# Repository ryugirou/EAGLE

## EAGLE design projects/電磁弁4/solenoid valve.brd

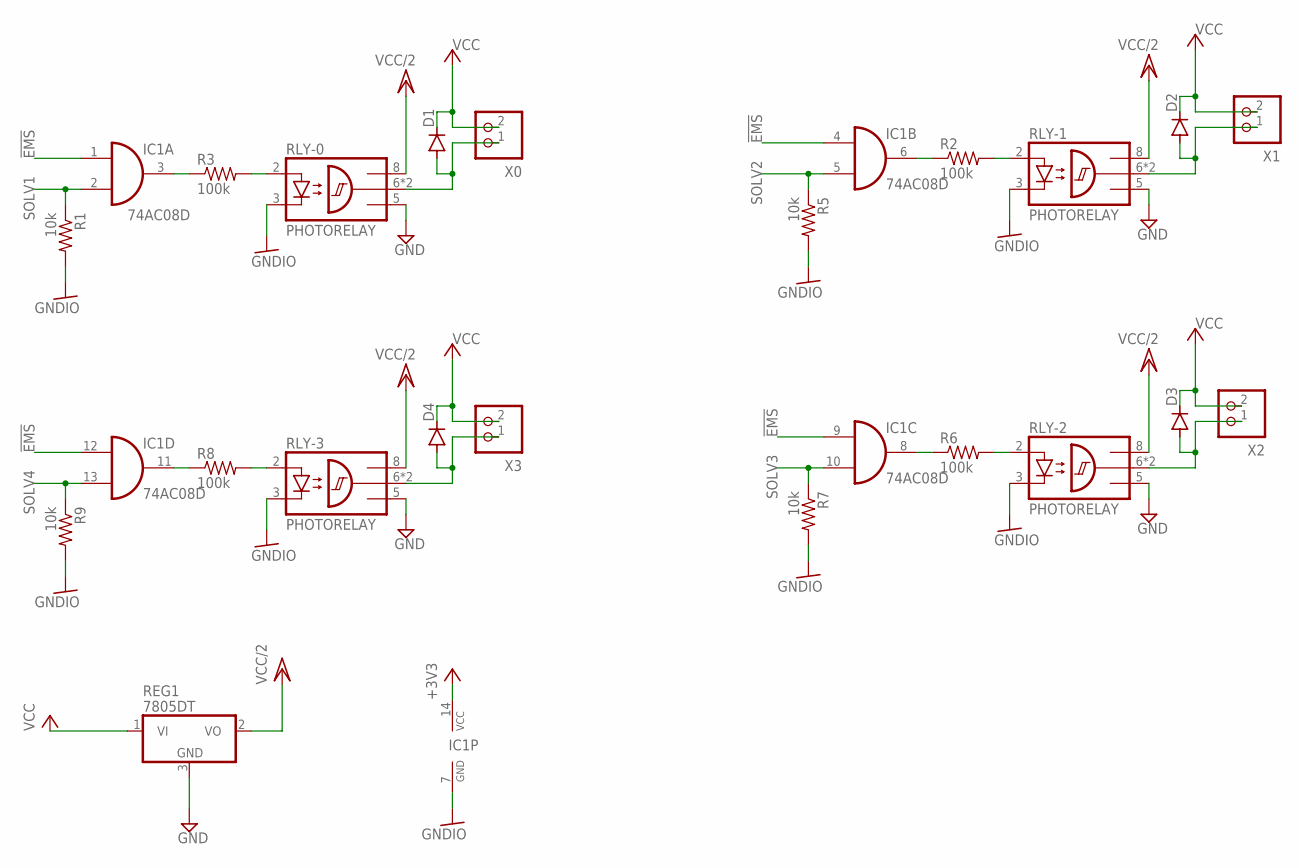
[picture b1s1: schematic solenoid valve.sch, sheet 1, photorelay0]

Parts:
D1, D2, D3, D4: DIODE-SOD123; SOD123
IC1: 74AC08D; SO14
R1, R5, R7, R9: 10k; R0603
R2, R3, R6, R8: 100k; R0603
REG1: 7805DT; TO252
RLY-0, RLY-1, RLY-2, RLY-3: PHOTORELAY; SOP254P1016X385-8
X0, X1, X2, X3: S2B-XH-A

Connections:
!EMS: IC1.1 (I0), IC1.4 (I0), IC1.9 (I0), IC1.12 (I0); also elsewhere on the board
+3V3: IC1.14 (VCC); also elsewhere on the board
GND: REG1.3 (GND), RLY-0.5 (GND), RLY-1.5 (GND), RLY-2.5 (GND), RLY-3.5 (GND); also elsewhere on the board
GNDIO: IC1.7 (GND), R1.2, R5.2, R7.2, R9.2, RLY-0.3 (C), RLY-1.3 (C), RLY-2.3 (C), RLY-3.3 (C); also elsewhere on the board
unnamed: D2.A, RLY-1.6 (OUT), RLY-1.7 (OUT), X1.1
unnamed: R2.2, RLY-1.2 (A)
unnamed: D1.A, RLY-0.6 (OUT), RLY-0.7 (OUT), X0.1
unnamed: IC1.6 (O), R2.1
unnamed: D3.A, RLY-2.6 (OUT), RLY-2.7 (OUT), X2.1
unnamed: R3.2, RLY-0.2 (A)
unnamed: IC1.3 (O), R3.1
unnamed: R6.2, RLY-2.2 (A)
unnamed: IC1.8 (O), R6.1
unnamed: D4.A, RLY-3.6 (OUT), RLY-3.7 (OUT), X3.1
unnamed: R8.2, RLY-3.2 (A)
unnamed: IC1.11 (O), R8.1
SOLV1: IC1.2 (I1), R1.1; also elsewhere on the board
SOLV2: IC1.5 (I1), R5.1; also elsewhere on the board
SOLV3: IC1.10 (I1), R7.1; also elsewhere on the board
SOLV4: IC1.13 (I1), R9.1; also elsewhere on the board
VCC: D1.C, D2.C, D3.C, D4.C, REG1.1 (VI), X0.2, X1.2, X2.2, X3.2; also elsewhere on the board
VCC/2: REG1.2 (VO), RLY-0.8 (VCC), RLY-1.8 (VCC), RLY-2.8 (VCC), RLY-3.8 (VCC); also elsewhere on the board

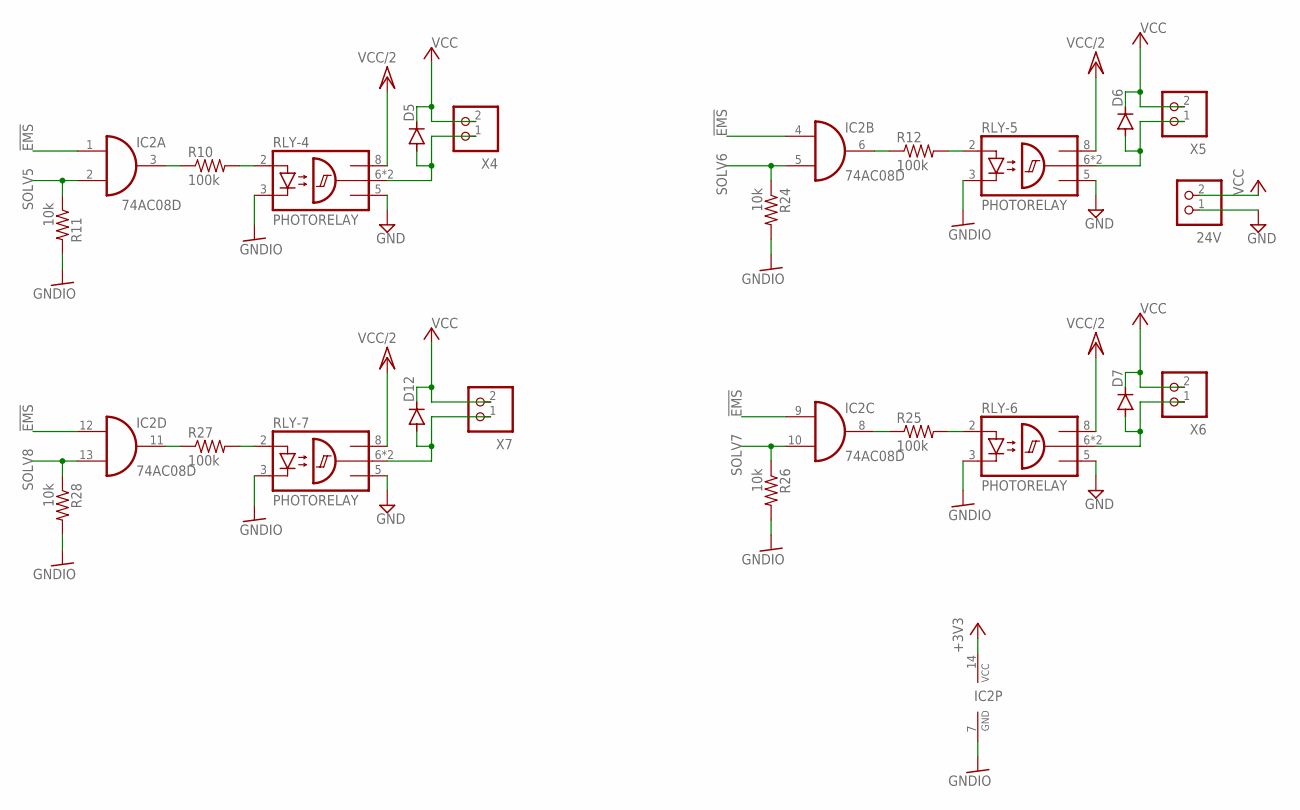
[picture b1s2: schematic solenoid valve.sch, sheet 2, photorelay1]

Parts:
24V: S2B-XH-A
D5, D6, D7, D12: DIODE-SOD123; SOD123
IC2: 74AC08D; SO14
R10, R12, R25, R27: 100k; R0603
R11, R24, R26, R28: 10k; R0603
RLY-4, RLY-5, RLY-6, RLY-7: PHOTORELAY; SOP254P1016X385-8
X4, X5, X6, X7: S2B-XH-A

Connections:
!EMS: IC2.1 (I0), IC2.4 (I0), IC2.9 (I0), IC2.12 (I0); also elsewhere on the board
+3V3: IC2.14 (VCC); also elsewhere on the board
GND: 24V.1, RLY-4.5 (GND), RLY-5.5 (GND), RLY-6.5 (GND), RLY-7.5 (GND); also elsewhere on the board
GNDIO: IC2.7 (GND), R11.2, R24.2, R26.2, R28.2, RLY-4.3 (C), RLY-5.3 (C), RLY-6.3 (C), RLY-7.3 (C); also elsewhere on the board
unnamed: D5.A, RLY-4.6 (OUT), RLY-4.7 (OUT), X4.1
unnamed: R10.2, RLY-4.2 (A)
unnamed: IC2.3 (O), R10.1
unnamed: D6.A, RLY-5.6 (OUT), RLY-5.7 (OUT), X5.1
unnamed: R12.2, RLY-5.2 (A)
unnamed: IC2.6 (O), R12.1
unnamed: D7.A, RLY-6.6 (OUT), RLY-6.7 (OUT), X6.1
unnamed: R25.2, RLY-6.2 (A)
unnamed: IC2.8 (O), R25.1
unnamed: D12.A, RLY-7.6 (OUT), RLY-7.7 (OUT), X7.1
unnamed: R27.2, RLY-7.2 (A)
unnamed: IC2.11 (O), R27.1
SOLV5: IC2.2 (I1), R11.1; also elsewhere on the board
SOLV6: IC2.5 (I1), R24.1; also elsewhere on the board
SOLV7: IC2.10 (I1), R26.1; also elsewhere on the board
SOLV8: IC2.13 (I1), R28.1; also elsewhere on the board
VCC: 24V.2, D5.C, D6.C, D7.C, D12.C, X4.2, X5.2, X6.2, X7.2; also elsewhere on the board
VCC/2: RLY-4.8 (VCC), RLY-5.8 (VCC), RLY-6.8 (VCC), RLY-7.8 (VCC); also elsewhere on the board

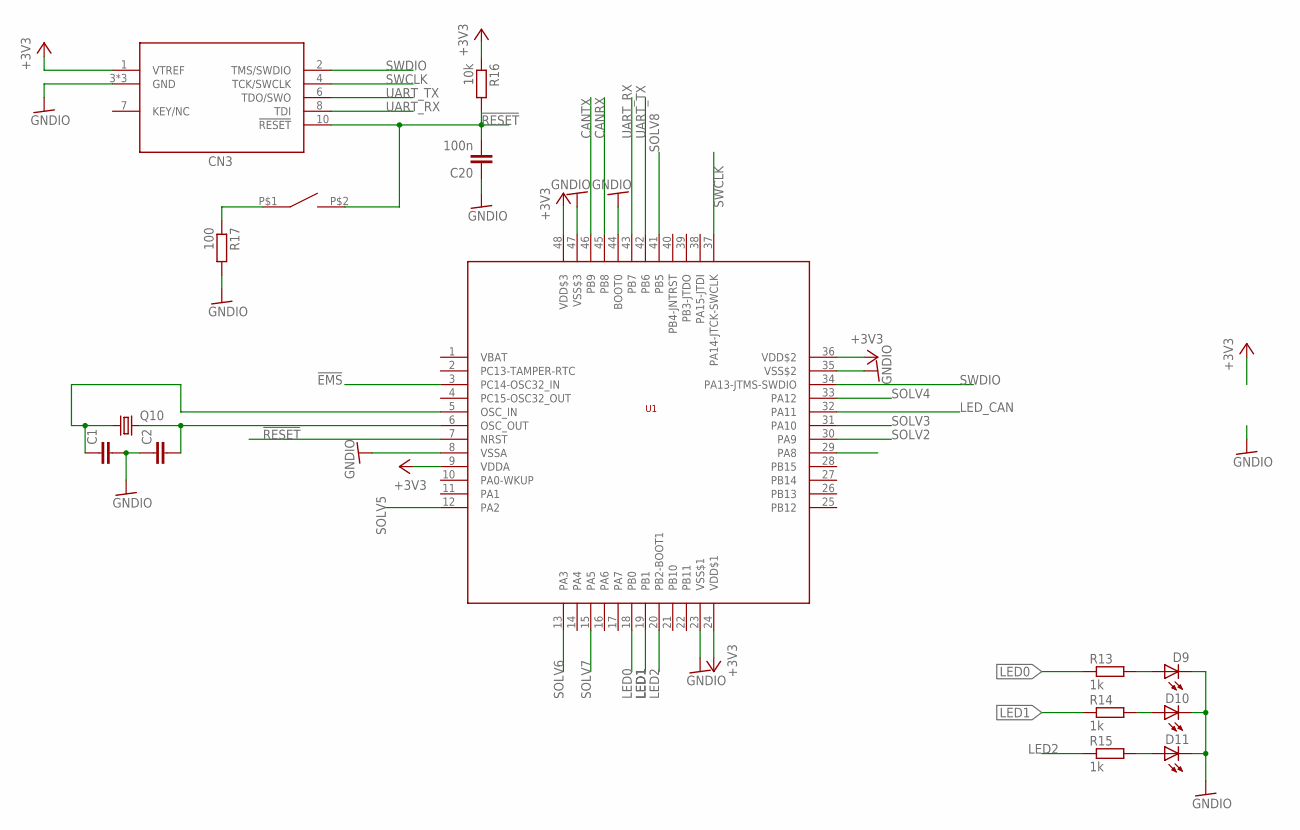
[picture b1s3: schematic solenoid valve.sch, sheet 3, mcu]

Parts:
C1, C2: C-EUC0603; C0603
C20: 100n; C0603
CN3: CON_SWD_1.27_SMD
D9, D10, D11: LEDCHIPLED_0805; CHIPLED_0805
Q10: CRYSTALHC49UP; HC49UP
R13, R14, R15: 1k; R0603
R16: 10k; R0603
R17: 100; R0603
SW1: SWITCH_TACTILETOP; SWITCH_TACTILE_3X6
U1: STM32F103C8; LQFP48

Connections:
!EMS: U1.3 (PC14-OSC32_IN); also elsewhere on the board
!RESET: C20.2, CN3.10 (!RESET), R16.2, SW1.P$2 (2), U1.7 (NRST)
+3V3: CN3.1 (VTREF), R16.1, U1.9 (VDDA), U1.24 (VDD$1), U1.36 (VDD$2), U1.48 (VDD$3); also elsewhere on the board
CANRX: U1.45 (PB8); also elsewhere on the board
CANTX: U1.46 (PB9); also elsewhere on the board
GNDIO: C1.2, C2.1, C20.1, CN3.3 (GND), CN3.5 (GND), CN3.9 (GND), D9.C, D10.C, D11.C, R17.2, U1.8 (VSSA), U1.23 (VSS$1), U1.35 (VSS$2), U1.44 (BOOT0), U1.47 (VSS$3); also elsewhere on the board
LED0: R13.1, U1.18 (PB0)
LED1: R14.1, U1.19 (PB1)
LED2: R15.1, U1.20 (PB2-BOOT1)
LED_CAN: U1.32 (PA11); also elsewhere on the board
unnamed: D10.A, R14.2
unnamed: D9.A, R13.2
unnamed: C2.2, Q10.2, U1.6 (OSC_OUT)
unnamed: R17.1, SW1.P$1 (1)
unnamed: C1.1, Q10.1, U1.5 (OSC_IN)
unnamed: D11.A, R15.2
SOLV1: U1.29 (PA8); also elsewhere on the board
SOLV2: U1.30 (PA9); also elsewhere on the board
SOLV3: U1.31 (PA10); also elsewhere on the board
SOLV4: U1.33 (PA12); also elsewhere on the board
SOLV5: U1.12 (PA2); also elsewhere on the board
SOLV6: U1.13 (PA3); also elsewhere on the board
SOLV7: U1.15 (PA5); also elsewhere on the board
SOLV8: U1.41 (PB5); also elsewhere on the board
SWCLK: CN3.4 (TCK/SWCLK), U1.37 (PA14-JTCK-SWCLK)
SWDIO: CN3.2 (TMS/SWDIO), U1.34 (PA13-JTMS-SWDIO)
UART_RX: CN3.8 (TDI), U1.43 (PB7)
UART_TX: CN3.6 (TDO/SWO), U1.42 (PB6)

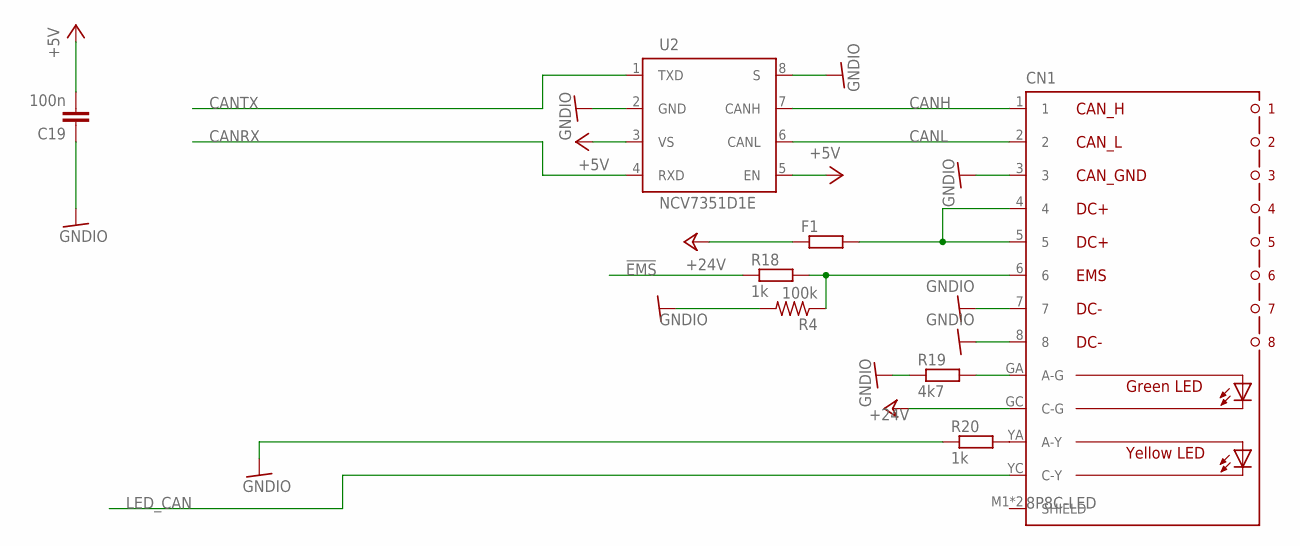
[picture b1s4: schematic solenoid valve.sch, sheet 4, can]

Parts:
C19: 100n; C0603
CN1: 8P8C-LED
F1: R-EU_R1206; R1206
R4: 100k; R0603
R18, R20: 1k; R0603
R19: 4k7; R0603
U2: NCV7351D1E; SO08

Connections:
!EMS: R18.1; also elsewhere on the board
+5V: C19.2, U2.3 (VS), U2.5 (EN); also elsewhere on the board
+24V: CN1.GC (C-G), F1.1; also elsewhere on the board
CANH: CN1.1, U2.7 (CANH)
CANL: CN1.2, U2.6 (CANL)
CANRX: U2.4 (RXD); also elsewhere on the board
CANTX: U2.1 (TXD); also elsewhere on the board
GNDIO: C19.1, CN1.3, CN1.7, CN1.8, R4.2, R19.1, R20.1, U2.2 (GND), U2.8 (S); also elsewhere on the board
LED_CAN: CN1.YC (C-Y); also elsewhere on the board
unnamed: CN1.4, CN1.5, F1.2
unnamed: CN1.YA (A-Y), R20.2
unnamed: CN1.GA (A-G), R19.2
unnamed: CN1.6, R4.1, R18.2

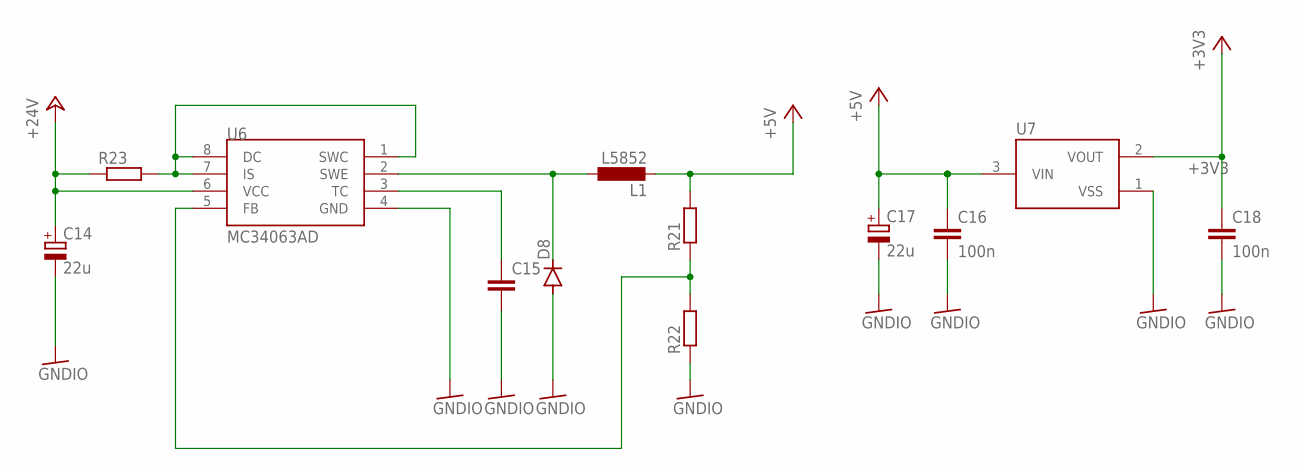
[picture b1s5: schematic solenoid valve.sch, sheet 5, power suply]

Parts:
C14, C17: 22u; E2-5
C15: C-EUC0603; C0603
C16, C18: 100n; C0603
D8: DIODE-SOD123; SOD123
L1: L5852
R21, R22: R-EU_R0603; R0603
R23: R-EU_R1206; R1206
U6: MC34063AD; SOIC8
U7: XC6206; SOT95P240X110-3

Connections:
+3V3: C18.1, U7.2 (VOUT); also elsewhere on the board
+5V: C16.1, C17.+, L1.P$2 (2), R21.2, U7.3 (VIN); also elsewhere on the board
+24V: C14.+, R23.1, U6.6 (VCC); also elsewhere on the board
GNDIO: C14.-, C15.2, C16.2, C17.-, C18.2, D8.A, R22.1, U6.4 (GND), U7.1 (VSS); also elsewhere on the board
unnamed: R23.2, U6.1 (SWC), U6.7 (IS), U6.8 (DC)
unnamed: D8.C, L1.P$1 (1), U6.2 (SWE)
unnamed: C15.1, U6.3 (TC)
unnamed: R21.1, R22.2, U6.5 (FB)

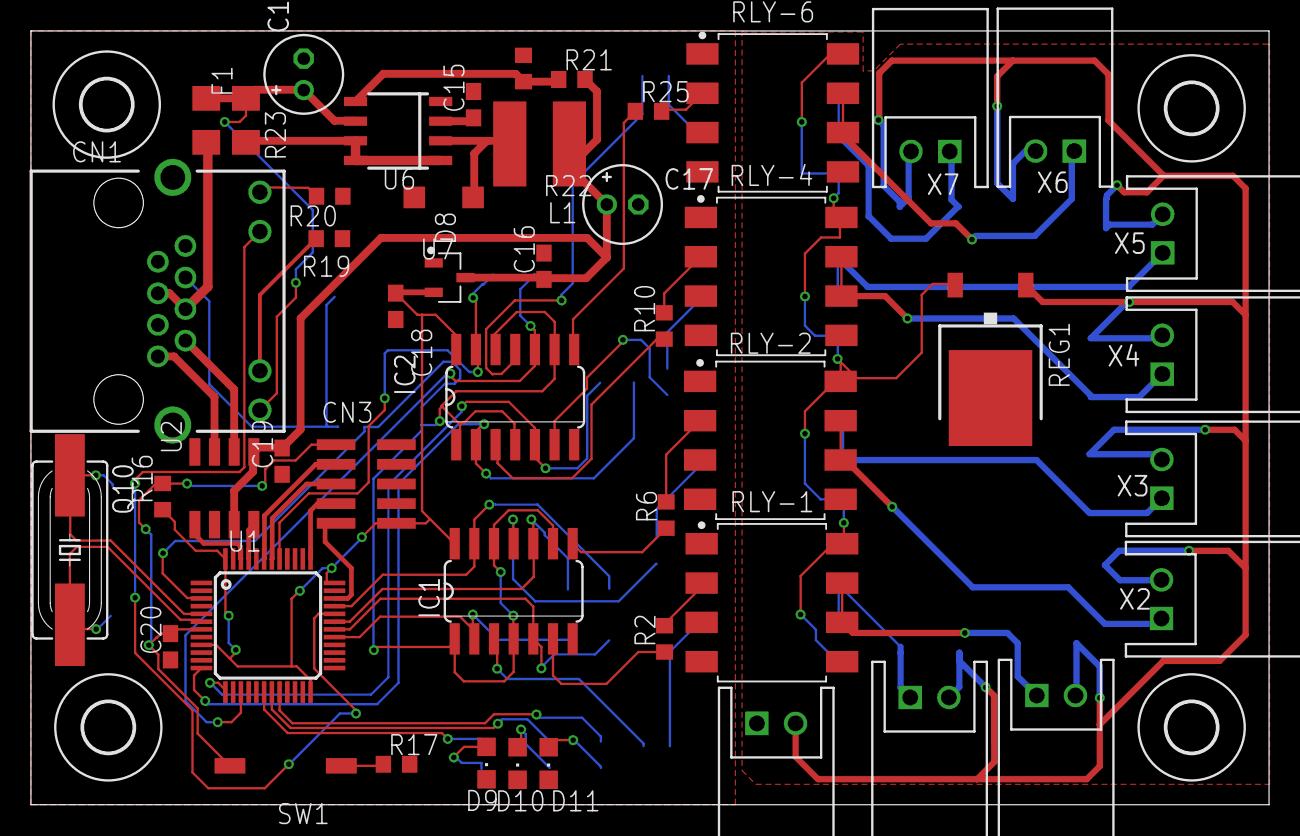
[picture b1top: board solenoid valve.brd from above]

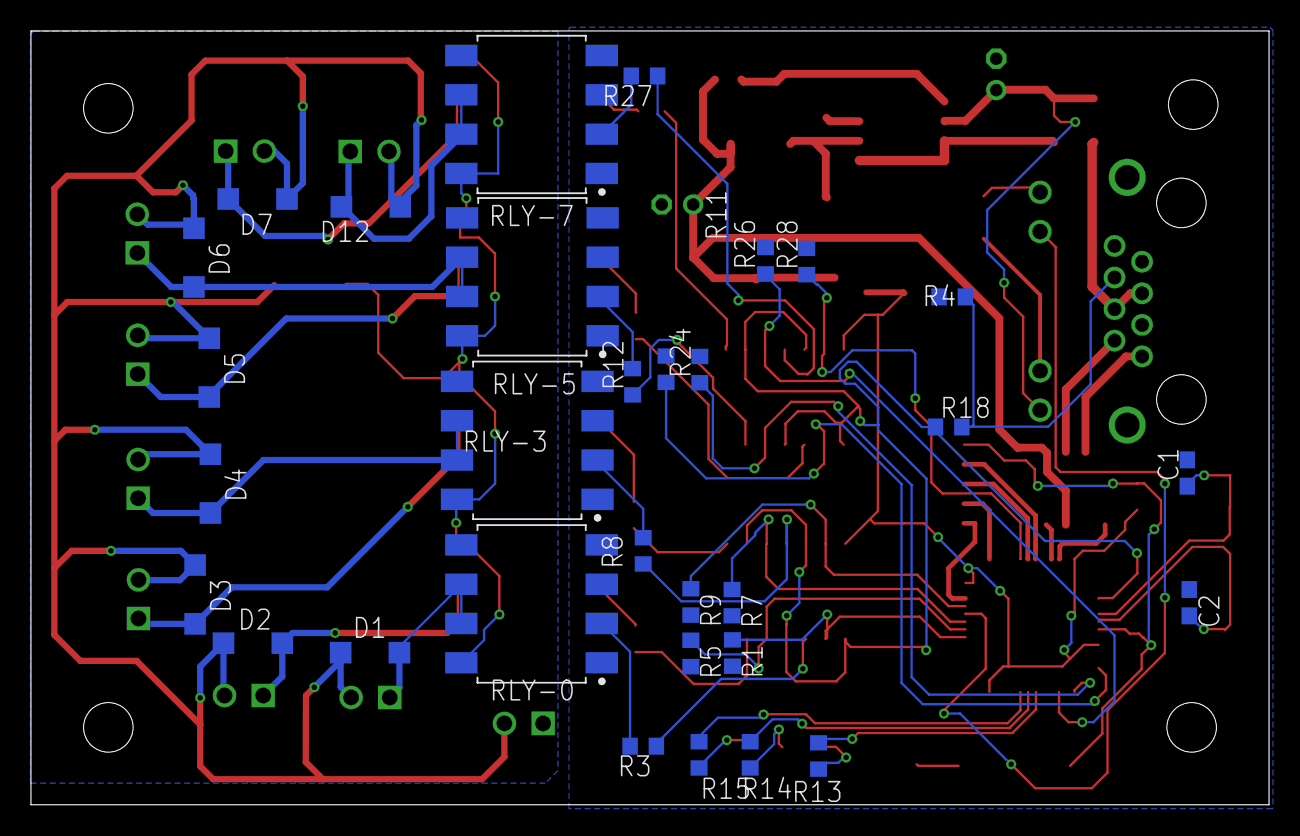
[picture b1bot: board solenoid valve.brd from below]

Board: 2 copper layers, 80.0 x 50.0 mm, 83 parts (31 on the bottom side), 67 nets.

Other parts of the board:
U$1, U$2, U$3, U$4: 3,2

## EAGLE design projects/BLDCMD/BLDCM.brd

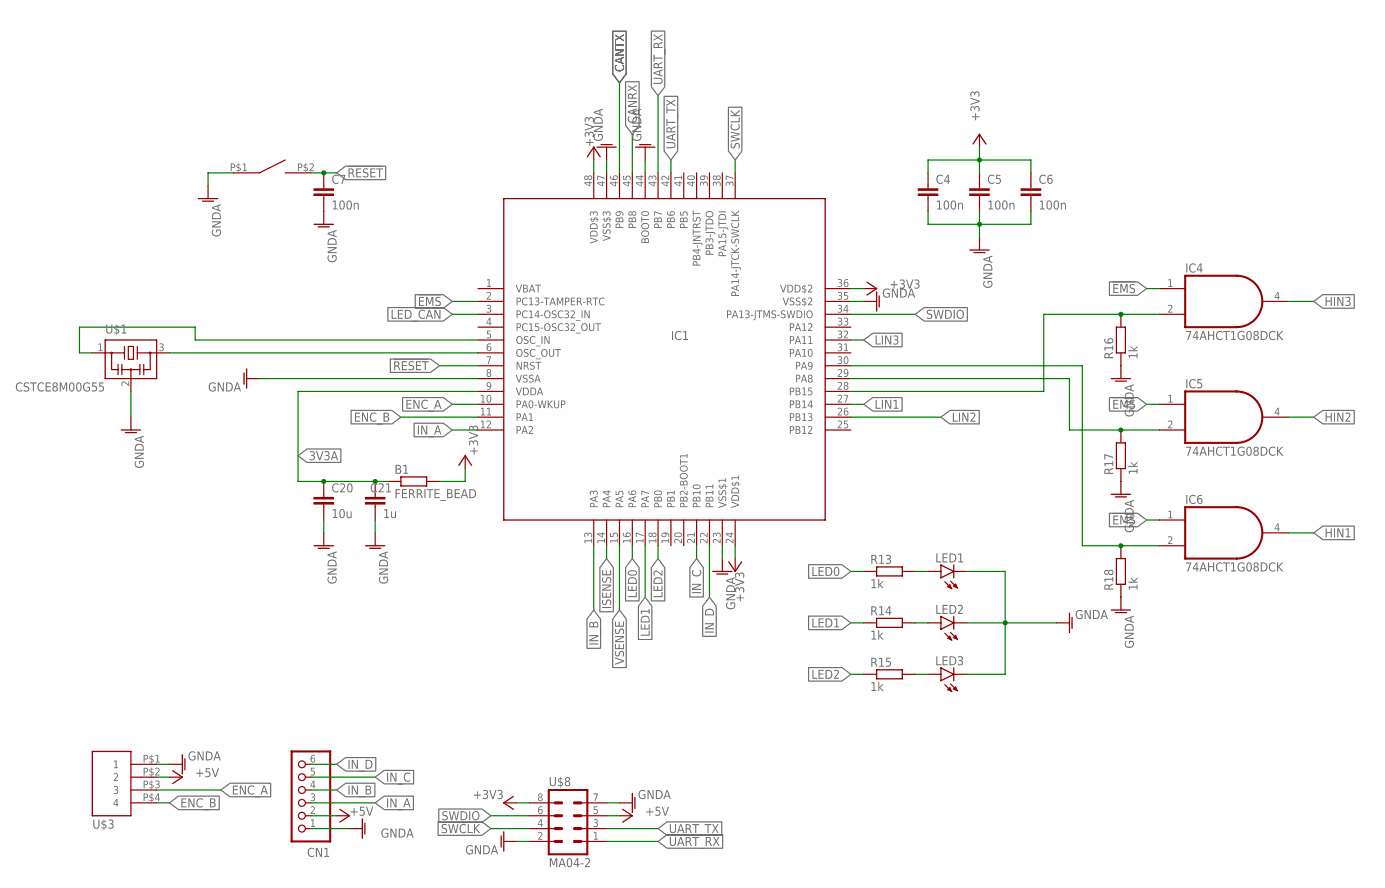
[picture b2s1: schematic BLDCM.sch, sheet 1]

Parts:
B1: FERRITE_BEAD; R0603
C4, C5, C6, C7: 100n; C0603
C20: 10u; C0603
C21: 1u; C0603
CN1: S6B-XH-A
IC1: STM32F103C8; LQFP48
IC4, IC5, IC6: 74AHCT1G08DCK; SC70-5
LED1, LED2, LED3: LEDCHIP-LED0805; CHIP-LED0805
R13, R14, R15, R16, R17, R18: 1k; R0603
U$1: CSTCE8M00G55
U$3: XH-4-SIDE; CON-XH-4-SIDE
U$4: SWITCH_TACTILETOP; SWITCH_TACTILE_3X6
U$8: MA04-2; MA04-2W

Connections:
3V3A: B1.1, C20.1, C21.1, IC1.9 (VDDA); also elsewhere on the board
!EMS: IC1.2 (PC13-TAMPER-RTC), IC4.1 (I0), IC5.1 (I0), IC6.1 (I0); also elsewhere on the board
!RESET: C7.1, IC1.7 (NRST), U$4.P$2 (2)
+3V3: B1.2, C4.1, C5.1, C6.1, IC1.24 (VDD$1), IC1.36 (VDD$2), IC1.48 (VDD$3), IC4.5 (+3V3), IC5.5 (+3V3), IC6.5 (+3V3), U$8.8; also elsewhere on the board
+5V: CN1.2, U$3.P$2 (2), U$8.5; also elsewhere on the board
CANRX: IC1.45 (PB8); also elsewhere on the board
CANTX: IC1.46 (PB9); also elsewhere on the board
ENC_A: IC1.10 (PA0-WKUP), U$3.P$3 (3)
ENC_B: IC1.11 (PA1), U$3.P$4 (4)
GNDA: C4.2, C5.2, C6.2, C7.2, C20.2, C21.2, CN1.1, IC1.8 (VSSA), IC1.23 (VSS$1), IC1.35 (VSS$2), IC1.44 (BOOT0), IC1.47 (VSS$3), IC4.3 (GNDA), IC5.3 (GNDA), IC6.3 (GNDA), LED1.C, LED2.C, LED3.C, R16.1, R17.1, R18.1, U$1.2, U$3.P$1 (1), U$4.P$1 (1), U$8.2, U$8.7; also elsewhere on the board
HIN1: IC6.4 (O); also elsewhere on the board
HIN2: IC5.4 (O); also elsewhere on the board
HIN3: IC4.4 (O); also elsewhere on the board
IN_A: CN1.3, IC1.12 (PA2)
IN_B: CN1.4, IC1.13 (PA3)
IN_C: CN1.5, IC1.21 (PB10)
IN_D: CN1.6, IC1.22 (PB11)
ISENSE: IC1.14 (PA4); also elsewhere on the board
LED0: IC1.16 (PA6), R13.1
LED1: IC1.17 (PA7), R14.1
LED2: IC1.18 (PB0), R15.1
LED_CAN: IC1.3 (PC14-OSC32_IN); also elsewhere on the board
LIN1: IC1.27 (PB14); also elsewhere on the board
LIN2: IC1.26 (PB13); also elsewhere on the board
LIN3: IC1.32 (PA11); also elsewhere on the board
unnamed: IC1.6 (OSC_OUT), U$1.3
unnamed: IC1.5 (OSC_IN), U$1.1
unnamed: IC1.30 (PA9), IC6.2 (I1), R18.2
unnamed: IC1.28 (PB15), IC4.2 (I1), R16.2
unnamed: IC1.29 (PA8), IC5.2 (I1), R17.2
unnamed: LED3.A, R15.2
unnamed: LED1.A, R13.2
unnamed: LED2.A, R14.2
SWCLK: IC1.37 (PA14-JTCK-SWCLK), U$8.4
SWDIO: IC1.34 (PA13-JTMS-SWDIO), U$8.6
UART_RX: IC1.43 (PB7), U$8.1
UART_TX: IC1.42 (PB6), U$8.3
VSENSE: IC1.15 (PA5); also elsewhere on the board

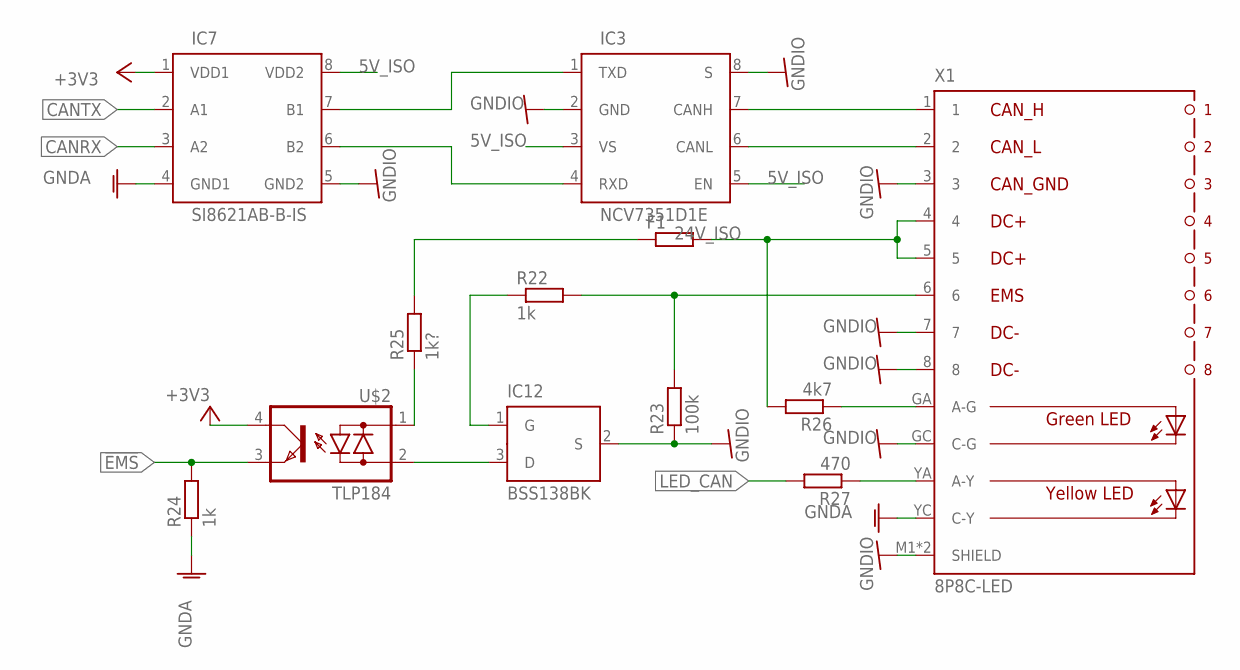
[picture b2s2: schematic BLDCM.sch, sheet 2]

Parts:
F1: R-EU_R1206; R1206
IC3: NCV7351D1E; SO08
IC7: SI8621AB-B-IS; SO08
IC12: BSS138BK; SOT23
R22, R24: 1k; R0603
R23: 100k; R0603
R25: 1k?; R0603
R26: 4k7; R0603
R27: 470; R0603
U$2: TLP184; 11-4M1S
X1: 8P8C-LED

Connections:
5V_ISO: IC3.3 (VS), IC3.5 (EN), IC7.8 (VDD2); also elsewhere on the board
24V_ISO: F1.1, R25.2; also elsewhere on the board
!EMS: R24.2, U$2.3 (E); also elsewhere on the board
+3V3: IC7.1 (VDD1), U$2.4 (C); also elsewhere on the board
CANRX: IC7.3 (A2); also elsewhere on the board
CANTX: IC7.2 (A1); also elsewhere on the board
GNDA: IC7.4 (GND1), R24.1, X1.YC (C-Y); also elsewhere on the board
GNDIO: IC3.2 (GND), IC3.8 (S), IC7.5 (GND2), IC12.2 (S), R23.1, X1.3, X1.7, X1.8, X1.GC (C-G), X1.M1 (SHIELD), X1.M2 (SHIELD); also elsewhere on the board
LED_CAN: R27.2; also elsewhere on the board
unnamed: IC3.1 (TXD), IC7.7 (B1)
unnamed: IC3.7 (CANH), X1.1
unnamed: IC3.6 (CANL), X1.2
unnamed: IC3.4 (RXD), IC7.6 (B2)
unnamed: R22.2, R23.2, X1.6
unnamed: F1.2, R26.2, X1.4, X1.5
unnamed: IC12.1 (G), R22.1
unnamed: IC12.3 (D), U$2.2 (AC2)
unnamed: R25.1, U$2.1 (AC1)
unnamed: R26.1, X1.GA (A-G)
unnamed: R27.1, X1.YA (A-Y)

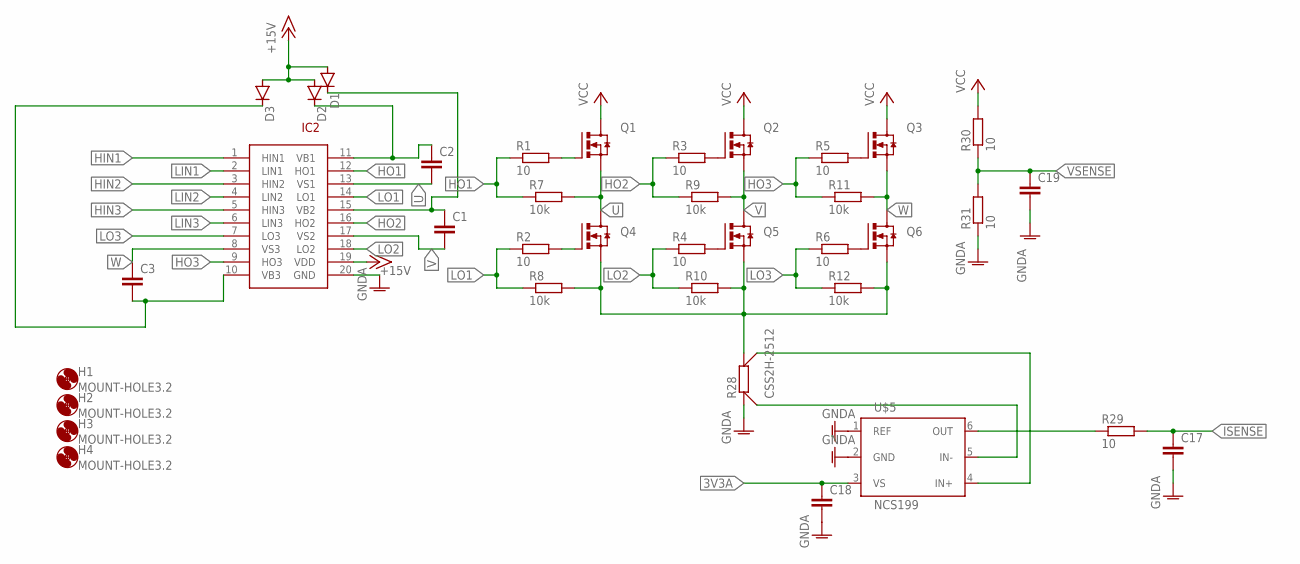
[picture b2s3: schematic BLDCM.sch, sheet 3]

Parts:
C1, C2, C3, C17, C18, C19: C-EUC0603; C0603
D1, D2, D3: DIODE-SOD323-R; SOD323-R
H1, H2, H3, H4: MOUNT-HOLE3.2; 3,2
IC2: FAN7888MX; SOIC20S
Q1, Q2, Q3, Q4, Q5, Q6: N-MOSFET-; SOT669
R1, R2, R3, R4, R5, R6, R29, R30, R31: 10; R0603
R7, R8, R9, R10, R11, R12: 10k; R0603
R28: CSS2H-2512
U$5: NCS199; SOT65P210X110-6

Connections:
3V3A: C18.1, U$5.3 (VS); also elsewhere on the board
+15V: D1.A, D2.A, D3.A, IC2.19 (VDD); also elsewhere on the board
GNDA: C17.2, C18.2, C19.2, IC2.20 (GND), R28.1$1 (1), R28.1$2 (1), R31.1, U$5.1 (REF), U$5.2 (GND); also elsewhere on the board
HIN1: IC2.1 (HIN1); also elsewhere on the board
HIN2: IC2.3 (HIN2); also elsewhere on the board
HIN3: IC2.5 (HIN3); also elsewhere on the board
HO1: IC2.12 (HO1), R1.1, R7.1
HO2: IC2.16 (HO2), R3.1, R9.1
HO3: IC2.9 (HO3), R5.1, R11.1
ISENSE: C17.1, R29.2; also elsewhere on the board
LIN1: IC2.2 (LIN1); also elsewhere on the board
LIN2: IC2.4 (LIN2); also elsewhere on the board
LIN3: IC2.6 (LIN3); also elsewhere on the board
LO1: IC2.14 (LO1), R2.1, R8.1
LO2: IC2.18 (LO2), R4.1, R10.1
LO3: IC2.7 (LO3), R6.1, R12.1
unnamed: C1.1, D1.C, IC2.15 (VB2)
unnamed: C2.1, D2.C, IC2.11 (VB1)
unnamed: C3.2, D3.C, IC2.10 (VB3)
unnamed: Q1.4 (GATE), R1.2
unnamed: Q4.4 (GATE), R2.2
unnamed: Q2.4 (GATE), R3.2
unnamed: Q5.4 (GATE), R4.2
unnamed: Q3.4 (GATE), R5.2
unnamed: Q6.4 (GATE), R6.2
unnamed: Q4.1 (SOURCE), Q4.2 (SOURCE), Q4.3 (SOURCE), Q5.1 (SOURCE), Q5.2 (SOURCE), Q5.3 (SOURCE), Q6.1 (SOURCE), Q6.2 (SOURCE), Q6.3 (SOURCE), R8.2, R10.2, R12.2, R28.2$1 (2), R28.2$2 (2)
unnamed: R28.2S, U$5.4 (IN+)
unnamed: R28.1S, U$5.5 (IN-)
unnamed: R29.1, U$5.6 (OUT)
U: C2.2, IC2.13 (VS1), Q1.1 (SOURCE), Q1.2 (SOURCE), Q1.3 (SOURCE), Q4.5 (DRAIN), R7.2
V: C1.2, IC2.17 (VS2), Q2.1 (SOURCE), Q2.2 (SOURCE), Q2.3 (SOURCE), Q5.5 (DRAIN), R9.2
VCC: Q1.5 (DRAIN), Q2.5 (DRAIN), Q3.5 (DRAIN), R30.2; also elsewhere on the board
VSENSE: C19.1, R30.1, R31.2; also elsewhere on the board
W: C3.1, IC2.8 (VS3), Q3.1 (SOURCE), Q3.2 (SOURCE), Q3.3 (SOURCE), Q6.5 (DRAIN), R11.2

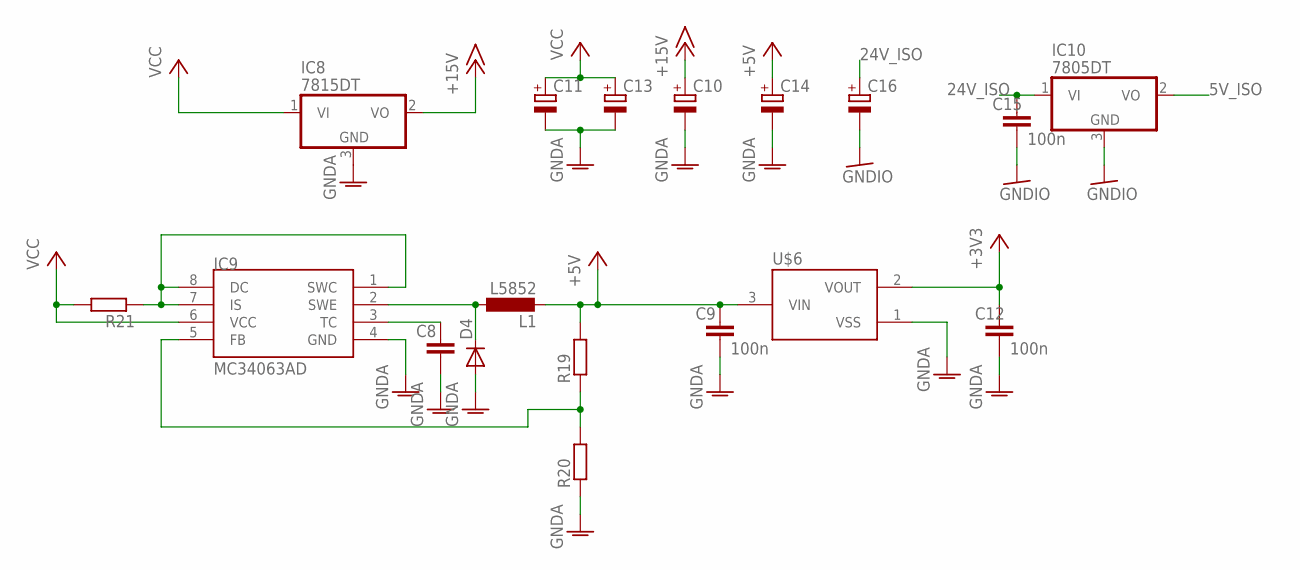
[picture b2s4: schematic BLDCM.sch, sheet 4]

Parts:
C8: C-EUC0603; C0603
C9, C12, C15: 100n; C0603
C10, C14, C16: CPOL-EUE2.5-5; E2,5-5
C11, C13: CPOL-EUE5-10.5; E5-10,5
D4: DIODE-SOD123; SOD123
IC8: 7815DT; TO252
IC9: MC34063AD; SOIC8
IC10: 7805DT; TO252
L1: L5852
R19, R20, R21: R-EU_R0603; R0603
U$6: XC6206; SOT95P240X110-3

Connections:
5V_ISO: IC10.2 (VO); also elsewhere on the board
24V_ISO: C15.1, C16.+, IC10.1 (VI); also elsewhere on the board
+3V3: C12.1, U$6.2 (VOUT); also elsewhere on the board
+5V: C9.1, C14.+, L1.P$2 (2), R19.2, U$6.3 (VIN); also elsewhere on the board
+15V: C10.+, IC8.2 (VO); also elsewhere on the board
GNDA: C8.2, C9.2, C10.-, C11.-, C12.2, C13.-, C14.-, D4.A, IC8.3 (GND), IC9.4 (GND), R20.1, U$6.1 (VSS); also elsewhere on the board
GNDIO: C15.2, C16.-, IC10.3 (GND); also elsewhere on the board
unnamed: D4.C, IC9.2 (SWE), L1.P$1 (1)
unnamed: IC9.5 (FB), R19.1, R20.2
unnamed: IC9.1 (SWC), IC9.7 (IS), IC9.8 (DC), R21.1
unnamed: C8.1, IC9.3 (TC)
VCC: C11.+, C13.+, IC8.1 (VI), IC9.6 (VCC), R21.2; also elsewhere on the board

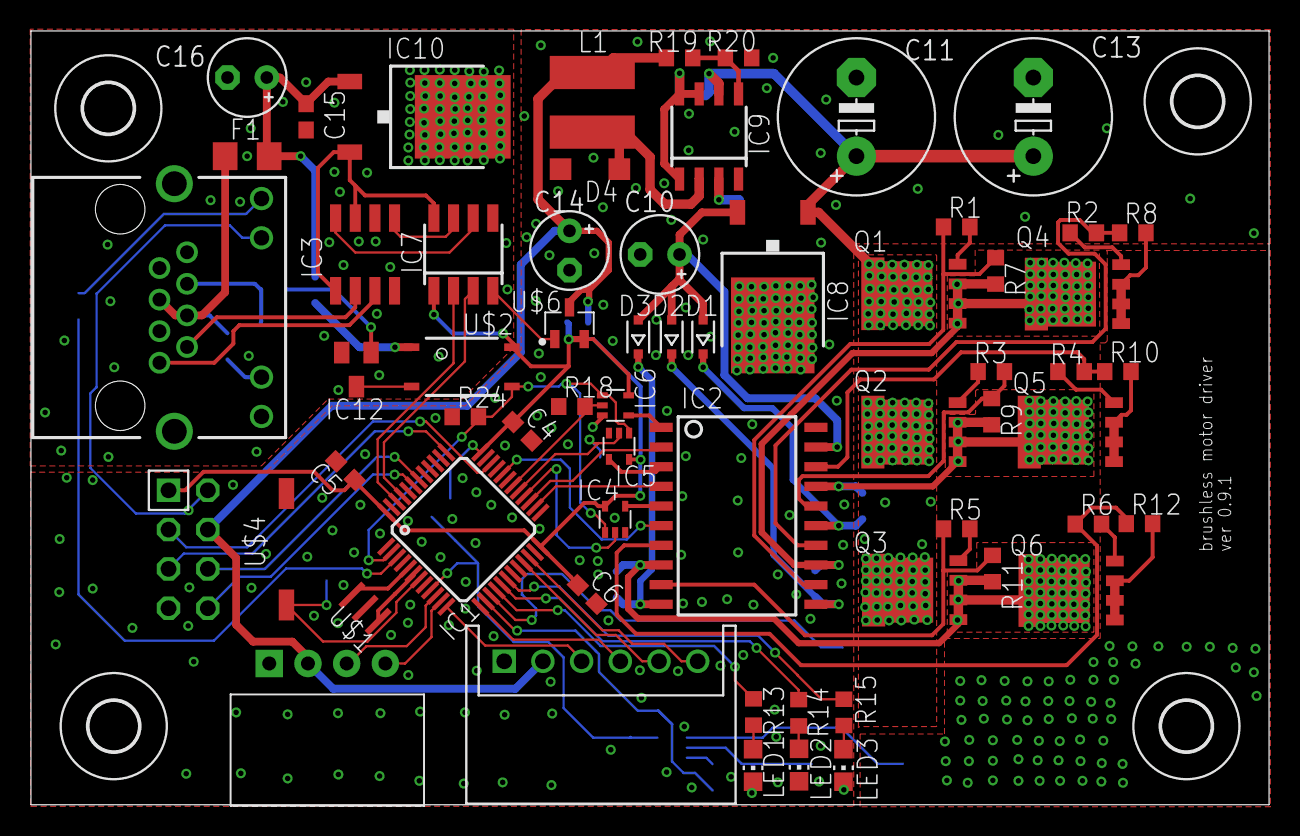
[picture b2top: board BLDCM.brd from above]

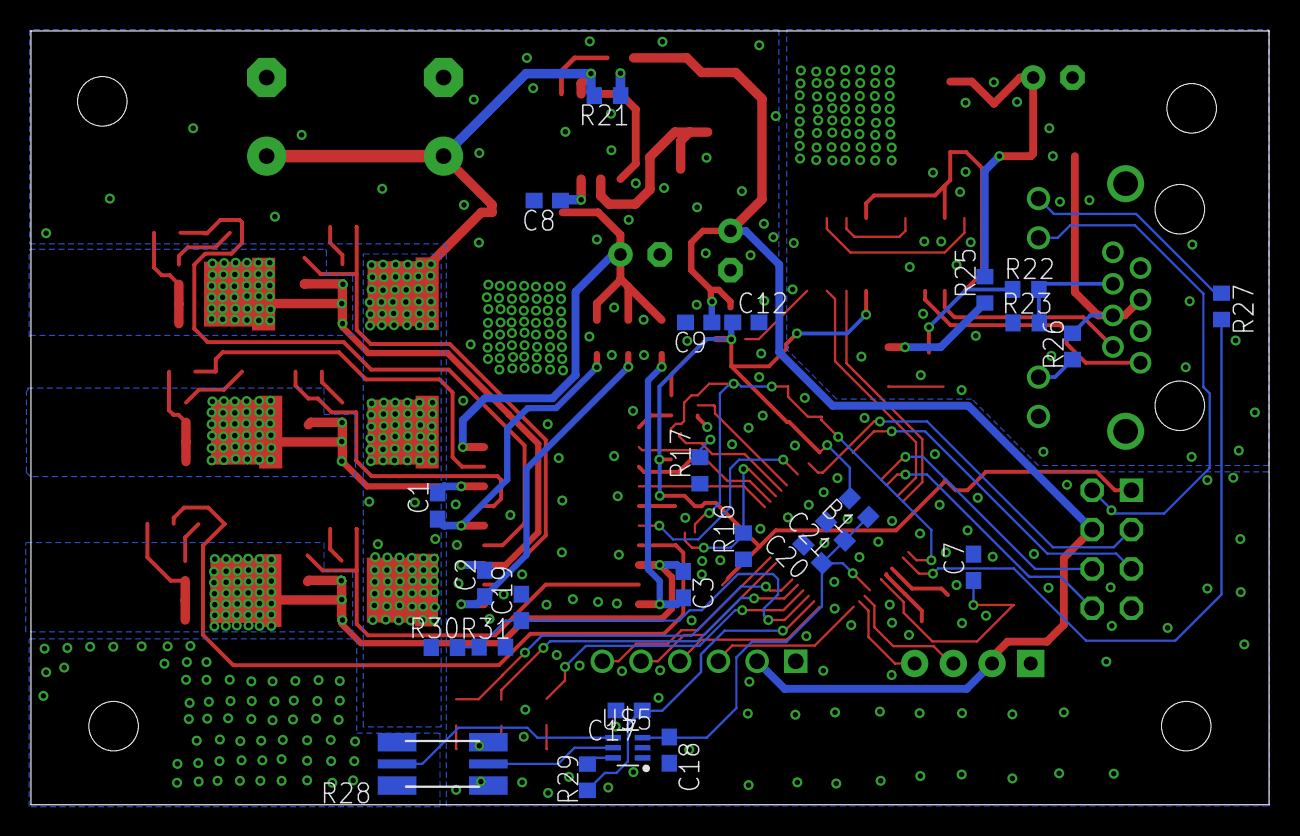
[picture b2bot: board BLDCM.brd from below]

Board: 2 copper layers, 80.0 x 50.0 mm, 92 parts (26 on the bottom side), 80 nets.

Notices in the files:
parts and their libraries:
con-molex-usb: (C) 2014 Tomasz Boleslaw CEDRO, cederom@tlen.pl, http://www.tomek.cedro.info.
